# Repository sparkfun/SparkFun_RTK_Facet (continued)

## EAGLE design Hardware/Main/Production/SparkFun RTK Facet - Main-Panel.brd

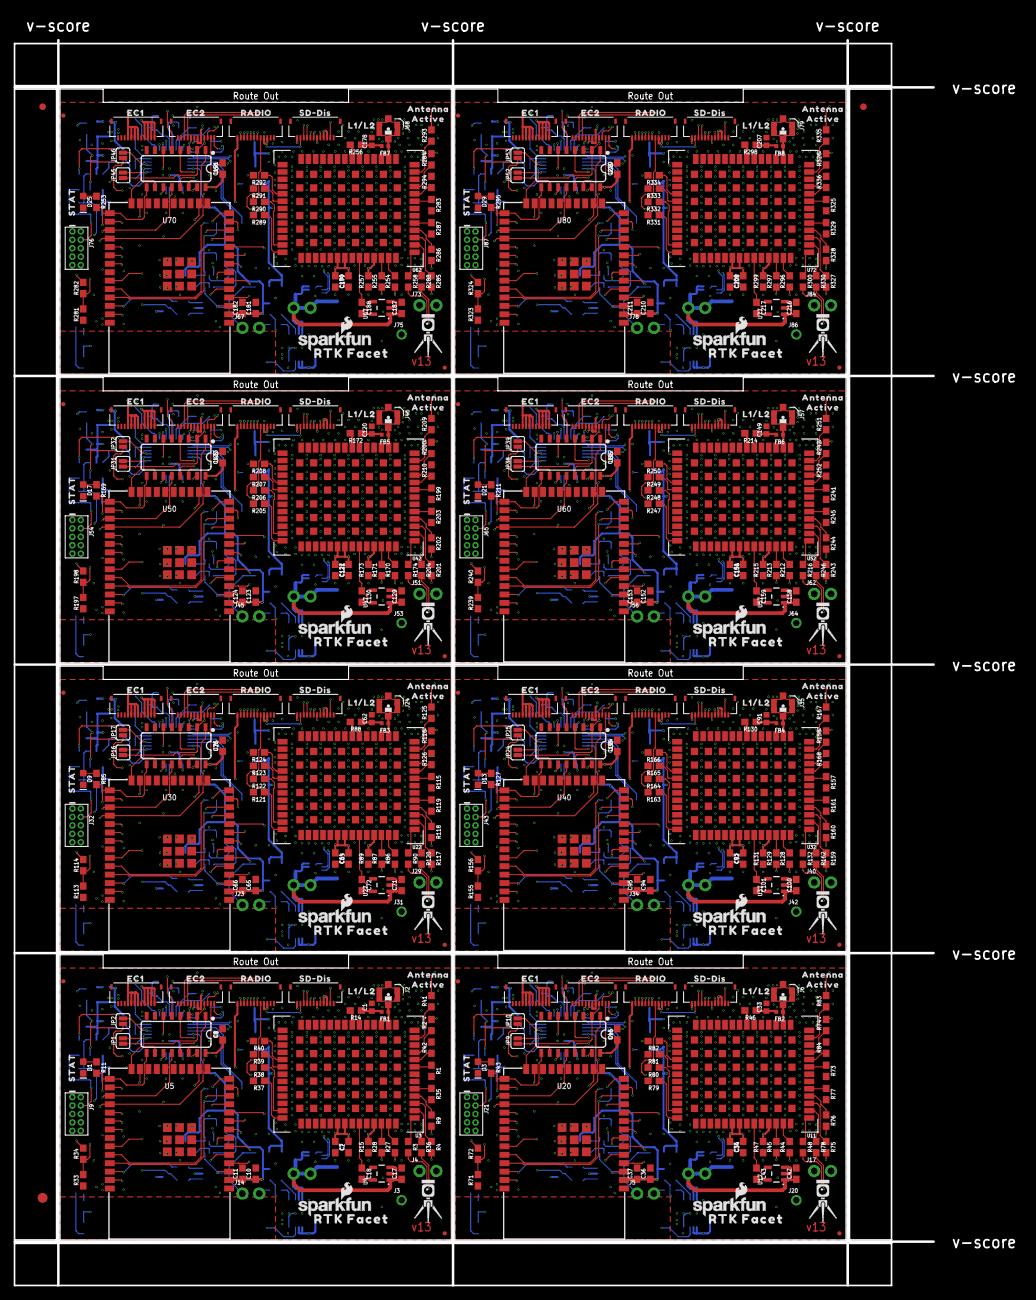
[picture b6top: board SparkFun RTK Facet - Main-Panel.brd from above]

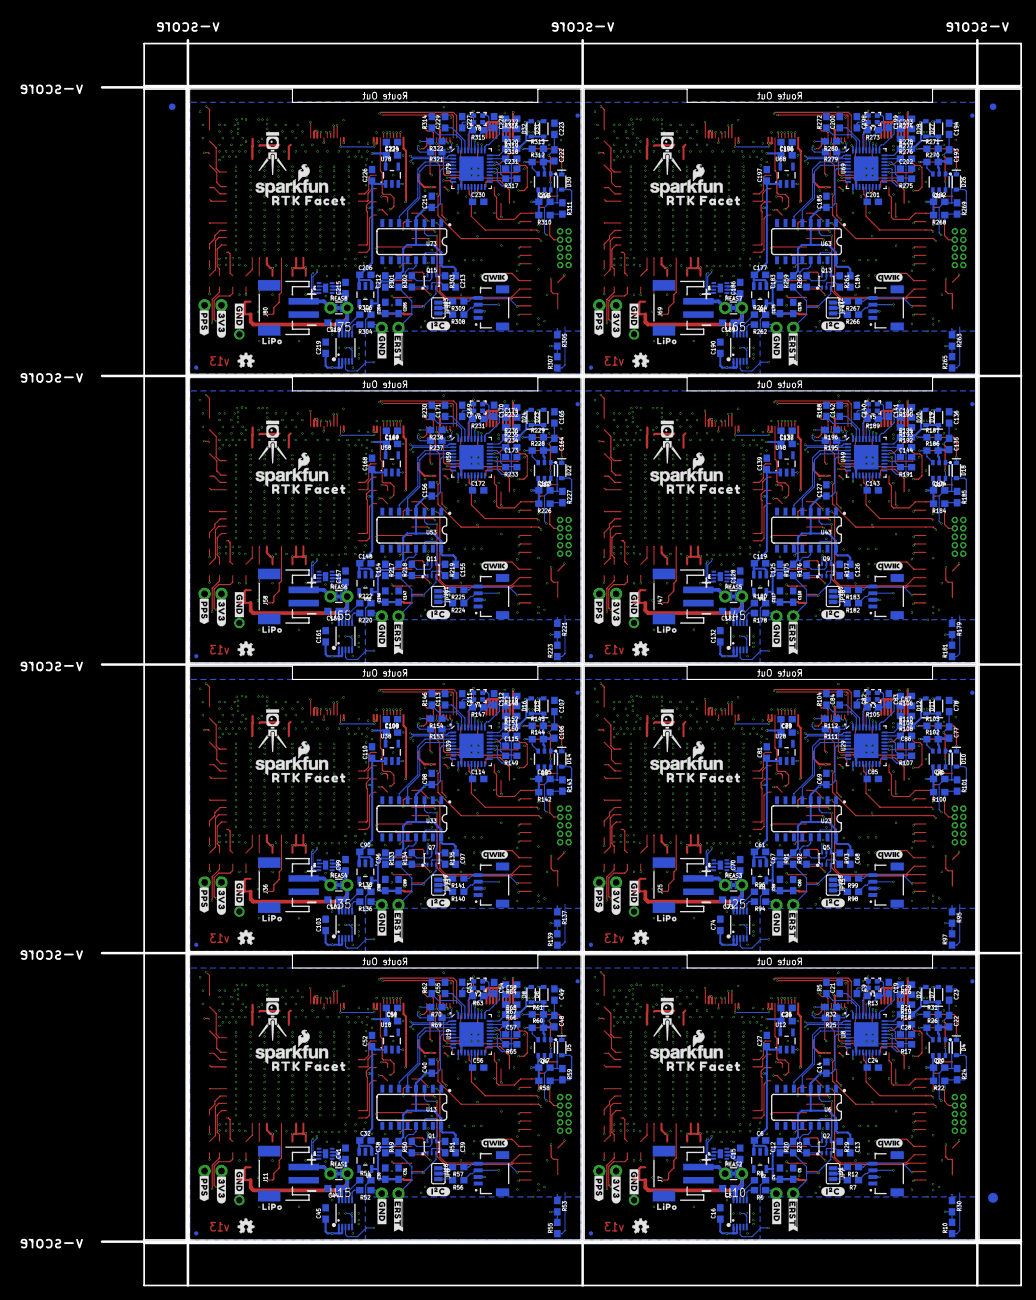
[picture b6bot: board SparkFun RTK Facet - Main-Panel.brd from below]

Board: 4 copper layers, 138.6 x 187.7 mm, 1054 parts (587 on the bottom side), 736 nets.

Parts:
C1, C33, C62, C91, C120, C149, C178, C207: 47pF; 0402
C2, C4, C6, C17, C18, C25, C27, C30, C32, C34, C42, C43, C50, C52, C59, C61, C63, C71, C72, C79, C81, C88, C90, C92, C100, C101, C108, C110, C117, C119, C121, C129, C130, C137, C139, C146, C148, C150, C158, C159, C166, C168, C175, C177, C179, C187, C188, C195, C197, C204, C206, C208, C216, C217, C224, C226: 1.0uF; 0603
C3, C16, C44, C45, C73, C74, C102, C103, C131, C132, C160, C161, C189, C190, C218, C219: 4.7uF; 0603
C5, C7, C8, C11, C12, C13, C15, C21, C22, C23, C24, C26, C28, C29, C31, C35, C37, C38, C39, C41, C46, C48, C49, C51, C55, C56, C57, C58, C60, C64, C66, C67, C68, C70, C75, C77, C78, C80, C84, C85, C86, C87, C89, C93, C95, C96, C97, C99, C104, C106, C107, C109, C113, C114, C115, C116, C118, C122, C124, C125, C126, C128, C133, C135, C136, C138, C142, C143, C144, C145, C147, C151, C153, C154, C155, C157, C162, C164, C165, C167, C171, C172, C173, C174, C176, C180, C182, C183, C184, C186, C191, C193, C194, C196, C200, C201, C202, C203, C205, C209, C211, C212, C213, C215, C220, C222, C223, C225, C229, C230, C231, C232: 0.1uF; 0603
C9, C19, C53, C54, C82, C83, C111, C112, C140, C141, C169, C170, C198, C199, C227, C228: 18pF; 0603
C10, C14, C20, C36, C40, C47, C65, C69, C76, C94, C98, C105, C123, C127, C134, C152, C156, C163, C181, C185, C192, C210, C214, C221: 10uF; 0603
D1, D3, D9, D13, D17, D21, D25, D29: Yellow; LED-0603
D2, D6, D7, D8, D11, D12, D15, D16, D19, D20, D23, D24, D27, D28, D31, D32: 3A/10V/280mV; SOD-323
D4, D5, D10, D14, D18, D22, D26, D30: 250mA/100V; SOD-323
E$1, E$2, E$3, E$4: FIDUCIAL-1X2
E$5, E$6: FIDUCIAL-1.5X3
FB1, FB2, FB3, FB4, FB5, FB6, FB7, FB8: 2.66Ω; 0402-TIGHT
J1, J16, J28, J39, J50, J61, J72, J83: QWIIC_RIGHT_ANGLE; JST04_1MM_RA
J2, J6, J24, J35, J46, J57, J68, J79: U.FL
J3, J20, J31, J42, J53, J64, J75, J86: 1X01_NO_SILK
J4, J5, J14, J17, J23, J29, J34, J40, J45, J51, J56, J62, J67, J73, J78, J84: 1X02_NO_SILK
J7, J11, J25, J36, J47, J58, J69, J80: JST-2-SMD
J8, J10, J12, J13, J15, J18, J19, J22, J26, J27, J30, J33, J37, J38, J41, J44, J48, J49, J52, J55, J59, J60, J63, J66, J70, J71, J74, J77, J81, J82, J85, J88: FPC_12_DOUBLESIDED_BACKFLIP
J9, J21, J32, J43, J54, J65, J76, J87: CORTEX_JTAG_DEBUG_PTH; 2X5-PTH-1.27MM
JP1, JP2, JP9, JP10, JP16, JP17, JP24, JP25, JP31, JP32, JP38, JP39, JP45, JP46, JP52, JP53: JUMPER-SMT_2_NO_SILK; SMT-JUMPER_2_NO_SILK
JP3, JP4, JP5, JP6, JP11, JP12, JP13, JP14, JP18, JP19, JP20, JP21, JP22, JP26, JP27, JP28, JP29, JP33, JP34, JP35, JP36, JP40, JP41, JP42, JP43, JP47, JP48, JP49, JP50, JP61, JP71, JP81: FIDUCIALUFIDUCIAL; FIDUCIAL-MICRO
JP7, JP8, JP15, JP23, JP30, JP37, JP44, JP51: JUMPER-SMT_3_NO_SILK; SMT-JUMPER_3_NO_SILK
LOGO1, LOGO4, LOGO7, LOGO10, LOGO13, LOGO16, LOGO19, LOGO22: OSHW-LOGOMINI; OSHW-LOGO-MINI
LOGO2, LOGO3, LOGO5, LOGO6, LOGO8, LOGO9, LOGO11, LOGO12, LOGO14, LOGO15, LOGO17, LOGO18, LOGO20, LOGO21, LOGO23, LOGO24: SFE_LOGO_NAME_FLAME.1_INCH; SFE_LOGO_NAME_FLAME_.1
MEAS1, MEAS2, MEAS3, MEAS4, MEAS5, MEAS6, MEAS7, MEAS8: JUMPER-COMBO_2_NC_TRACE; COMBO-JUMPER_2_NC_TRACE
Q1, Q2, Q5, Q7, Q9, Q11, Q13, Q15: MBT3904DW1T1; SC70-6
Q3, Q4, Q6, Q8, Q10, Q12, Q14, Q16: SIL2308; SOT26
R1, R2, R3, R4, R9, R35, R36, R37, R38, R39, R40, R41, R42, R48, R73, R74, R75, R76, R77, R78, R79, R80, R81, R82, R83, R84, R90, R115, R116, R117, R118, R119, R120, R121, R122, R123, R124, R125, R126, R132, R157, R158, R159, R160, R161, R162, R163, R164, R165, R166, R167, R168, R174, R199, R200, R201, R202, R203, R204, R205, R206, R207, R208, R209, R210, R216, R241, R242, R243, R244, R245, R246, R247, R248, R249, R250, R251, R252, R258, R283, R284, R285, R286, R287, R288, R289, R290, R291, R292, R293, R294, R300, R325, R326, R327, R328, R329, R330, R331, R332, R333, R334, R335, R336: 33; 0603
R5, R62, R104, R146, R188, R230, R272, R314: 12k; 0603
R6, R11, R43, R52, R85, R94, R127, R136, R169, R178, R211, R220, R253, R262, R295, R304: 1k; 0603
R7, R12, R56, R57, R98, R99, R140, R141, R182, R183, R224, R225, R266, R267, R308, R309: 2.2k; 0603
R8, R54, R96, R138, R180, R222, R264, R306: 0; 0603
R10, R20, R22, R23, R29, R31, R33, R34, R49, R50, R51, R55, R58, R61, R71, R72, R91, R92, R93, R97, R100, R103, R113, R114, R133, R134, R135, R139, R142, R145, R155, R156, R175, R176, R177, R181, R184, R187, R197, R198, R217, R218, R219, R223, R226, R229, R239, R240, R259, R260, R261, R265, R268, R271, R281, R282, R301, R302, R303, R307, R310, R313, R323, R324: 10k; 0603
R13, R63, R105, R147, R189, R231, R273, R315: 1M; 0603
R14, R46, R88, R130, R172, R214, R256, R298: 10; 0603
R15, R16, R17, R18, R19, R21, R26, R47, R60, R64, R65, R66, R67, R68, R89, R102, R106, R107, R108, R109, R110, R131, R144, R148, R149, R150, R151, R152, R173, R186, R190, R191, R192, R193, R194, R215, R228, R232, R233, R234, R235, R236, R257, R270, R274, R275, R276, R277, R278, R299, R312, R316, R317, R318, R319, R320: 100k; 0603
R24, R59, R101, R143, R185, R227, R269, R311: 300k; 0603
R25, R32, R69, R70, R111, R112, R153, R154, R195, R196, R237, R238, R279, R280, R321, R322: 22Ω; 0603
R27, R28, R44, R45, R86, R87, R128, R129, R170, R171, R212, R213, R254, R255, R296, R297: 27; 0603
R30, R53, R95, R137, R179, R221, R263, R305: 150k; 0603
U1, U16, U26, U36, U46, U56, U66, U76: 74HC4052D; SO16
U2, U9, U12, U18, U21, U28, U31, U38, U41, U48, U51, U58, U61, U68, U71, U78: AP2112K-3.3V; SOT23-5
U3, U11, U22, U32, U42, U52, U62, U72: U-BLOX_ZED-F9P; ZED-F9P
U4, U17, U27, U37, U47, U57, U67, U77: STLQ015; SOT23-5
U5, U20, U30, U40, U50, U60, U70, U80: ESP-WROOM-3232D-DFMP; ESP-WROOM-32D-DFM_PASTE
U6, U13, U23, U33, U43, U53, U63, U73: CH340C; SO016
U7, U14, U24, U34, U44, U54, U64, U74: MAX17048; DFN-8
U8, U19, U29, U39, U49, U59, U69, U79: USB251XB; QFN-36
U10, U15, U25, U35, U45, U55, U65, U75: MCP73833MSOP; MSOP10
U$1, U$21, U$45, U$65, U$86, U$106, U$126, U$146: LIPO0
U$2, U$30, U$40, U$60, U$80, U$101, U$121, U$141: QWIIC_4MM
U$3, U$19, U$43, U$63, U$83, U$104, U$124, U$144: EC21
U$4, U$20, U$44, U$64, U$85, U$105, U$125, U$145: SD#DIS0
U$5, U$22, U$46, U$66, U$87, U$107, U$127, U$147: ACTIVE1
U$6, U$28, U$49, U$69, U$90, U$110, U$130, U$150: #3V3#0
U$7, U$23, U$47, U$67, U$88, U$108, U$128, U$148: ANTENNA2
U$8, U$18, U$42, U$62, U$82, U$103, U$123, U$143: EC10
U$9, U$27, U$48, U$68, U$89, U$109, U$129, U$149: L1#L20
U$10, U$29, U$50, U$70, U$91, U$111, U$131, U$151: #PPS#1
U$11, U$13, U$34, U$36, U$54, U$56, U$74, U$76, U$95, U$97, U$115, U$117, U$135, U$137, U$155, U$157: RTK_FACET0
U$12, U$35, U$55, U$75, U$96, U$116, U$136, U$156: RADIO0
U$14, U$17, U$37, U$41, U$57, U$61, U$77, U$81, U$84, U$98, U$102, U$118, U$122, U$138, U$142, U$158: #GND#1
U$15, U$16, U$38, U$39, U$58, U$59, U$78, U$79, U$99, U$100, U$119, U$120, U$139, U$140, U$159, U$160: RTK5#SVG0
U$24, U$31, U$51, U$71, U$92, U$112, U$132, U$152: STAT0
U$25, U$32, U$52, U$72, U$93, U$113, U$133, U$153: #I�C#0
U$26, U$33, U$53, U$73, U$94, U$114, U$134, U$154: ##ERST##0
Y1, Y2, Y3, Y4, Y5, Y6, Y7, Y8: 24MHz; CRYSTAL-SMD-2.0X1.6MM

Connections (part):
3.3V: C2.1, C7.2, C8.1, C25.1, C26.2, J1.2, J4.1, J8.3, J8.4, J10.3, J10.4, J18.5, J18.6, JP7.2, R15.2, U1.16, U3.33, U3.34, U3.38, U12.5
3.3V1: C34.1, C35.2, C46.1, C50.1, C51.2, J13.5, J13.6, J16.2, J17.1, J19.3, J19.4, J22.3, J22.4, JP8.2, R47.2, U11.33, U11.34, U11.38, U16.16, U18.5
3.3V2: C63.1, C64.2, C75.1, C79.1, C80.2, J27.5, J27.6, J28.2, J29.1, J30.3, J30.4, J33.3, J33.4, JP15.2, R89.2, U22.33, U22.34, U22.38, U26.16, U28.5
3.3V3: C92.1, C93.2, C104.1, C108.1, C109.2, J38.5, J38.6, J39.2, J40.1, J41.3, J41.4, J44.3, J44.4, JP23.2, R131.2, U32.33, U32.34, U32.38, U36.16, U38.5
3.3V4: C121.1, C122.2, C133.1, C137.1, C138.2, J49.5, J49.6, J50.2, J51.1, J52.3, J52.4, J55.3, J55.4, JP30.2, R173.2, U42.33, U42.34, U42.38, U46.16, U48.5
3.3V5: C150.1, C151.2, C162.1, C166.1, C167.2, J60.5, J60.6, J61.2, J62.1, J63.3, J63.4, J66.3, J66.4, JP37.2, R215.2, U52.33, U52.34, U52.38, U56.16, U58.5
3.3V6: C179.1, C180.2, C191.1, C195.1, C196.2, J71.5, J71.6, J72.2, J73.1, J74.3, J74.4, J77.3, J77.4, JP44.2, R257.2, U62.33, U62.34, U62.38, U66.16, U68.5
3.3V7: C208.1, C209.2, C220.1, C224.1, C225.2, J82.5, J82.6, J83.2, J84.1, J85.3, J85.4, J88.3, J88.4, JP51.2, R299.2, U72.33, U72.34, U72.38, U76.16, U78.5
ANT_VCC: C1.1, FB1.2, R14.1
ANT_VCC1: C33.1, FB2.2, R46.1
ANT_VCC2: C62.1, FB3.2, R88.1
ANT_VCC3: C91.1, FB4.2, R130.1
ANT_VCC4: C120.1, FB5.2, R172.1
ANT_VCC5: C149.1, FB6.2, R214.1
ANT_VCC6: C178.1, FB7.2, R256.1
ANT_VCC7: C207.1, FB8.2, R298.1
CHG_LED: J8.11, U10.3
CHG_LED1: J19.11, U15.3
CHG_LED2: J30.11, U25.3
CHG_LED3: J41.11, U35.3
CHG_LED4: J52.11, U45.3
CHG_LED5: J63.11, U55.3
CHG_LED6: J74.11, U65.3
CHG_LED7: J85.11, U75.3
CHG_THERM1: R8.2, R10.2, R30.2
CHG_THERM2: R53.2, R54.2, R55.2
CHG_THERM3: R95.2, R96.2, R97.2
CHG_THERM4: R137.2, R138.2, R139.2
CHG_THERM5: R179.2, R180.2, R181.2
CHG_THERM6: R221.2, R222.2, R223.2
CHG_THERM7: R263.2, R264.2, R265.2
CHG_THERM8: R305.2, R306.2, R307.2
ESP32_!DTR: Q2.1, R23.1, U6.13
ESP32_!DTR1: Q1.1, R50.1, U13.13
ESP32_!DTR2: Q5.1, R92.1, U23.13
ESP32_!DTR3: Q7.1, R134.1, U33.13
ESP32_!DTR4: Q9.1, R176.1, U43.13
ESP32_!DTR5: Q11.1, R218.1, U53.13
ESP32_!DTR6: Q13.1, R260.1, U63.13
ESP32_!DTR7: Q15.1, R302.1, U73.13
ESP32_!RTS: Q2.4, R29.1, U6.14
ESP32_!RTS1: Q1.4, R51.1, U13.14
ESP32_!RTS2: Q5.4, R93.1, U23.14
ESP32_!RTS3: Q7.4, R135.1, U33.14
ESP32_!RTS4: Q9.4, R177.1, U43.14
ESP32_!RTS5: Q11.4, R219.1, U53.14
ESP32_!RTS6: Q13.4, R261.1, U63.14
ESP32_!RTS7: Q15.4, R303.1, U73.14
ESP32_EN: C12.1, J9.10, J14.1, Q2.3, R20.1, U5.3
ESP32_EN1: C38.1, J5.1, J21.10, Q1.3, R49.1, U20.3
ESP32_EN2: C67.1, J23.1, J32.10, Q5.3, R91.1, U30.3
ESP32_EN3: C96.1, J34.1, J43.10, Q7.3, R133.1, U40.3
ESP32_EN4: C125.1, J45.1, J54.10, Q9.3, R175.1, U50.3
ESP32_EN5: C154.1, J56.1, J65.10, Q11.3, R217.1, U60.3
ESP32_EN6: C183.1, J67.1, J76.10, Q13.3, R259.1, U70.3
ESP32_EN7: C212.1, J78.1, J87.10, Q15.3, R301.1, U80.3
ESP32_RXI: U5.34, U6.2
ESP32_RXI1: U13.2, U20.34
ESP32_RXI2: U23.2, U30.34
ESP32_RXI3: U33.2, U40.34
ESP32_RXI4: U43.2, U50.34
ESP32_RXI5: U53.2, U60.34
ESP32_RXI6: U63.2, U70.34
ESP32_RXI7: U73.2, U80.34
ESP32_TXO: U5.35, U6.3
ESP32_TXO1: U13.3, U20.35
ESP32_TXO2: U23.3, U30.35
ESP32_TXO3: U33.3, U40.35
ESP32_TXO4: U43.3, U50.35
ESP32_TXO5: U53.3, U60.35
ESP32_TXO6: U63.3, U70.35
ESP32_TXO7: U73.3, U80.35
ESP_0/BOOT/STAT_LED/MUX_B: Q2.6, R11.2, U1.9, U5.25
ESP_0/BOOT/STAT_LED/MUX_B1: Q1.6, R43.2, U16.9, U20.25
ESP_0/BOOT/STAT_LED/MUX_B2: Q5.6, R85.2, U26.9, U30.25
ESP_0/BOOT/STAT_LED/MUX_B3: Q7.6, R127.2, U36.9, U40.25
ESP_0/BOOT/STAT_LED/MUX_B4: Q9.6, R169.2, U46.9, U50.25
ESP_0/BOOT/STAT_LED/MUX_B5: Q11.6, R211.2, U56.9, U60.25
ESP_0/BOOT/STAT_LED/MUX_B6: Q13.6, R253.2, U66.9, U70.25
ESP_0/BOOT/STAT_LED/MUX_B7: Q15.6, R295.2, U76.9, U80.25
ESP_2/MUX_A: U1.10, U5.24
ESP_2/MUX_A1: U16.10, U20.24
ESP_2/MUX_A2: U26.10, U30.24
ESP_2/MUX_A3: U36.10, U40.24
ESP_2/MUX_A4: U46.10, U50.24
ESP_2/MUX_A5: U56.10, U60.24
ESP_2/MUX_A6: U66.10, U70.24
ESP_2/MUX_A7: U76.10, U80.24
ESP_3V1: C30.1, C31.2, C36.1, C37.1, C39.1, C40.1, J21.1, R49.2, R66.2, R72.2, U9.5, U13.4, U13.16, U19.5, U19.10, U19.15, U19.23, U19.29, U19.36, U20.2
ESP_3V2: C59.1, C60.2, C65.1, C66.1, C68.1, C69.1, J32.1, R91.2, R108.2, R114.2, U21.5, U23.4, U23.16, U29.5, U29.10, U29.15, U29.23, U29.29, U29.36, U30.2
ESP_3V3: C4.1, C5.2, C10.1, C11.1, C13.1, C14.1, J9.1, R18.2, R20.2, R34.2, U2.5, U5.2, U6.4, U6.16, U8.5, U8.10, U8.15, U8.23, U8.29, U8.36
ESP_3V4: C88.1, C89.2, C94.1, C95.1, C97.1, C98.1, J43.1, R133.2, R150.2, R156.2, U31.5, U33.4, U33.16, U39.5, U39.10, U39.15, U39.23, U39.29, U39.36, U40.2
ESP_3V5: C117.1, C118.2, C123.1, C124.1, C126.1, C127.1, J54.1, R175.2, R192.2, R198.2, U41.5, U43.4, U43.16, U49.5, U49.10, U49.15, U49.23, U49.29, U49.36, U50.2
ESP_3V6: C146.1, C147.2, C152.1, C153.1, C155.1, C156.1, J65.1, R217.2, R234.2, R240.2, U51.5, U53.4, U53.16, U59.5, U59.10, U59.15, U59.23, U59.29, U59.36, U60.2
ESP_3V7: C175.1, C176.2, C181.1, C182.1, C184.1, C185.1, J76.1, R259.2, R276.2, R282.2, U61.5, U63.4, U63.16, U69.5, U69.10, U69.15, U69.23, U69.29, U69.36, U70.2
ESP_3V8: C204.1, C205.2, C210.1, C211.1, C213.1, C214.1, J87.1, R301.2, R318.2, R324.2, U71.5, U73.4, U73.16, U79.5, U79.10, U79.15, U79.23, U79.29, U79.36, U80.2
ESP_4/RADIO_PWR_ON: J10.6, U5.26
ESP_4/RADIO_PWR_ON1: J22.6, U20.26
ESP_4/RADIO_PWR_ON2: J33.6, U30.26
ESP_4/RADIO_PWR_ON3: J44.6, U40.26
ESP_4/RADIO_PWR_ON4: J55.6, U50.26
ESP_4/RADIO_PWR_ON5: J66.6, U60.26
ESP_4/RADIO_PWR_ON6: J77.6, U70.26
ESP_4/RADIO_PWR_ON7: J88.6, U80.26
ESP_5/RADIO_CTSI: J10.8, U5.29
ESP_5/RADIO_CTSI1: J22.8, U20.29
ESP_5/RADIO_CTSI2: J33.8, U30.29
ESP_5/RADIO_CTSI3: J44.8, U40.29
ESP_5/RADIO_CTSI4: J55.8, U50.29
ESP_5/RADIO_CTSI5: J66.8, U60.29
ESP_5/RADIO_CTSI6: J77.8, U70.29
ESP_5/RADIO_CTSI7: J88.8, U80.29
ESP_12/MTDI: J9.8, U5.14
ESP_12/MTDI1: J21.8, U20.14
ESP_12/MTDI2: J32.8, U30.14
ESP_12/MTDI3: J43.8, U40.14
ESP_12/MTDI4: J54.8, U50.14
ESP_12/MTDI5: J65.8, U60.14
ESP_12/MTDI6: J76.8, U70.14
ESP_12/MTDI7: J87.8, U80.14
ESP_13/POWER_CTRL/MTCK: D4.A, J9.4, R22.1, R24.2, U5.16
ESP_13/POWER_CTRL/MTCK1: D5.A, J21.4, R58.1, R59.2, U20.16
ESP_13/POWER_CTRL/MTCK2: D10.A, J32.4, R100.1, R101.2, U30.16
ESP_13/POWER_CTRL/MTCK3: D14.A, J43.4, R142.1, R143.2, U40.16
ESP_13/POWER_CTRL/MTCK4: D18.A, J54.4, R184.1, R185.2, U50.16
ESP_13/POWER_CTRL/MTCK5: D22.A, J65.4, R226.1, R227.2, U60.16
ESP_13/POWER_CTRL/MTCK6: D26.A, J76.4, R268.1, R269.2, U70.16
ESP_13/POWER_CTRL/MTCK7: D30.A, J87.4, R310.1, R311.2, U80.16
ESP_14/PERIPHERAL_POWER/MTMS: J9.2, U5.13, U12.3
ESP_14/PERIPHERAL_POWER/MTMS1: J21.2, U18.3, U20.13
ESP_14/PERIPHERAL_POWER/MTMS2: J32.2, U28.3, U30.13
ESP_14/PERIPHERAL_POWER/MTMS3: J43.2, U38.3, U40.13
ESP_14/PERIPHERAL_POWER/MTMS4: J54.2, U48.3, U50.13
ESP_14/PERIPHERAL_POWER/MTMS5: J65.2, U58.3, U60.13
ESP_14/PERIPHERAL_POWER/MTMS6: J76.2, U68.3, U70.13
ESP_14/PERIPHERAL_POWER/MTMS7: J87.2, U78.3, U80.13
ESP_15/MTDO/RADIO_!RESET!: J9.6, J10.5, U5.23
ESP_15/MTDO/RADIO_!RESET!1: J21.6, J22.5, U20.23
ESP_15/MTDO/RADIO_!RESET!2: J32.6, J33.5, U30.23
ESP_15/MTDO/RADIO_!RESET!3: J43.6, J44.5, U40.23
ESP_15/MTDO/RADIO_!RESET!4: J54.6, J55.5, U50.23
ESP_15/MTDO/RADIO_!RESET!5: J65.6, J66.5, U60.23
ESP_15/MTDO/RADIO_!RESET!6: J76.6, J77.5, U70.23
ESP_15/MTDO/RADIO_!RESET!7: J87.6, J88.5, U80.23
ESP_16/ZED-TXO1: R3.2, U1.12, U5.27
ESP_16/ZED-TXO2: R48.2, U16.12, U20.27
ESP_16/ZED-TXO3: R90.2, U26.12, U30.27
ESP_16/ZED-TXO4: R132.2, U36.12, U40.27
ESP_16/ZED-TXO5: R174.2, U46.12, U50.27
ESP_16/ZED-TXO6: R216.2, U56.12, U60.27
ESP_16/ZED-TXO7: R258.2, U66.12, U70.27
ESP_16/ZED-TXO8: R300.2, U76.12, U80.27
ESP_17/ZED-RXI1: R36.2, U1.1, U5.28
ESP_17/ZED-RXI2: R78.2, U16.1, U20.28
ESP_17/ZED-RXI3: R120.2, U26.1, U30.28
ESP_17/ZED-RXI4: R162.2, U36.1, U40.28
ESP_17/ZED-RXI5: R204.2, U46.1, U50.28
ESP_17/ZED-RXI6: R246.2, U56.1, U60.28
ESP_17/ZED-RXI7: R288.2, U66.1, U70.28
ESP_17/ZED-RXI8: R330.2, U76.1, U80.28
ESP_18/SD_SCK: J8.7, U5.30
ESP_18/SD_SCK1: J19.7, U20.30
ESP_18/SD_SCK2: J30.7, U30.30
ESP_18/SD_SCK3: J41.7, U40.30
ESP_18/SD_SCK4: J52.7, U50.30
ESP_18/SD_SCK5: J63.7, U60.30
ESP_18/SD_SCK6: J74.7, U70.30
ESP_18/SD_SCK7: J85.7, U80.30
ESP_19/SD_CIPO: J8.8, U5.31
ESP_19/SD_CIPO1: J19.8, U20.31
ESP_19/SD_CIPO2: J30.8, U30.31
ESP_19/SD_CIPO3: J41.8, U40.31
ESP_19/SD_CIPO4: J52.8, U50.31
ESP_19/SD_CIPO5: J63.8, U60.31
ESP_19/SD_CIPO6: J74.8, U70.31
ESP_19/SD_CIPO7: J85.8, U80.31
ESP_21/SDA: J1.3, J8.10, J18.4, JP1.1, R4.2, R7.1, U1.2, U5.33, U7.8
ESP_21/SDA1: J13.4, J16.3, J19.10, JP9.1, R56.1, R75.2, U14.8, U16.2, U20.33
ESP_21/SDA2: J27.4, J28.3, J30.10, JP16.1, R98.1, R117.2, U24.8, U26.2, U30.33
ESP_21/SDA3: J38.4, J39.3, J41.10, JP24.1, R140.1, R159.2, U34.8, U36.2, U40.33
ESP_21/SDA4: J49.4, J50.3, J52.10, JP31.1, R182.1, R201.2, U44.8, U46.2, U50.33
ESP_21/SDA5: J60.4, J61.3, J63.10, JP38.1, R224.1, R243.2, U54.8, U56.2, U60.33
ESP_21/SDA6: J71.4, J72.3, J74.10, JP45.1, R266.1, R285.2, U64.8, U66.2, U70.33
ESP_21/SDA7: J82.4, J83.3, J85.10, JP52.1, R308.1, R327.2, U74.8, U76.2, U80.33
ESP_22/SCL: J1.4, J8.9, J18.3, JP2.1, R9.2, R12.1, U1.15, U5.36, U7.7
ESP_22/SCL1: J13.3, J16.4, J19.9, JP10.1, R57.1, R76.2, U14.7, U16.15, U20.36
ESP_22/SCL2: J27.3, J28.4, J30.9, JP17.1, R99.1, R118.2, U24.7, U26.15, U30.36
ESP_22/SCL3: J38.3, J39.4, J41.9, JP25.1, R141.1, R160.2, U34.7, U36.15, U40.36
ESP_22/SCL4: J49.3, J50.4, J52.9, JP32.1, R183.1, R202.2, U44.7, U46.15, U50.36
ESP_22/SCL5: J60.3, J61.4, J63.9, JP39.1, R225.1, R244.2, U54.7, U56.15, U60.36
ESP_22/SCL6: J71.3, J72.4, J74.9, JP46.1, R267.1, R286.2, U64.7, U66.15, U70.36
ESP_22/SCL7: J82.3, J83.4, J85.9, JP53.1, R309.1, R328.2, U74.7, U76.15, U80.36
ESP_23/SD_COPI: J8.6, U5.37
ESP_23/SD_COPI1: J19.6, U20.37
ESP_23/SD_COPI2: J30.6, U30.37
ESP_23/SD_COPI3: J41.6, U40.37
ESP_23/SD_COPI4: J52.6, U50.37
ESP_23/SD_COPI5: J63.6, U60.37
ESP_23/SD_COPI6: J74.6, U70.37
ESP_23/SD_COPI7: J85.6, U80.37
ESP_25/SD_!CS!: J8.5, U5.10
ESP_25/SD_!CS!1: J19.5, U20.10
ESP_25/SD_!CS!2: J30.5, U30.10
ESP_25/SD_!CS!3: J41.5, U40.10
ESP_25/SD_!CS!4: J52.5, U50.10
ESP_25/SD_!CS!5: J63.5, U60.10
ESP_25/SD_!CS!6: J74.5, U70.10
ESP_25/SD_!CS!7: J85.5, U80.10
ESP_26/DAC1: U16.11, U20.11
ESP_26/DAC2: U1.11, U5.11
ESP_26/DAC3: U26.11, U30.11
ESP_26/DAC4: U36.11, U40.11
ESP_26/DAC5: U46.11, U50.11
ESP_26/DAC6: U56.11, U60.11
ESP_26/DAC7: U66.11, U70.11
ESP_26/DAC8: U76.11, U80.11
ESP_27/FAST_OFF: C20.2, Q3.G1, R24.1, U5.12
ESP_27/FAST_OFF1: C47.2, Q4.G1, R59.1, U20.12
ESP_27/FAST_OFF2: C76.2, Q6.G1, R101.1, U30.12
ESP_27/FAST_OFF3: C105.2, Q8.G1, R143.1, U40.12
ESP_27/FAST_OFF4: C134.2, Q10.G1, R185.1, U50.12
ESP_27/FAST_OFF5: C163.2, Q12.G1, R227.1, U60.12
ESP_27/FAST_OFF6: C192.2, Q14.G1, R269.1, U70.12
ESP_27/FAST_OFF7: C221.2, Q16.G1, R311.1, U80.12
ESP_32/RADIO_TXO: J10.11, U5.8
ESP_32/RADIO_TXO1: J22.11, U20.8
ESP_32/RADIO_TXO2: J33.11, U30.8
ESP_32/RADIO_TXO3: J44.11, U40.8
ESP_32/RADIO_TXO4: J55.11, U50.8
ESP_32/RADIO_TXO5: J66.11, U60.8
ESP_32/RADIO_TXO6: J77.11, U70.8
ESP_32/RADIO_TXO7: J88.11, U80.8
ESP_33/RADIO_RXI: J10.10, U5.9
ESP_33/RADIO_RXI1: J22.10, U20.9
ESP_33/RADIO_RXI2: J33.10, U30.9
ESP_33/RADIO_RXI3: J44.10, U40.9
ESP_33/RADIO_RXI4: J55.10, U50.9
ESP_33/RADIO_RXI5: J66.10, U60.9
ESP_33/RADIO_RXI6: J77.10, U70.9
ESP_33/RADIO_RXI7: J88.10, U80.9
ESP_DM: U6.6, U8.3
ESP_DM1: U13.6, U19.3
ESP_DM2: U23.6, U29.3
ESP_DM3: U33.6, U39.3
ESP_DM4: U43.6, U49.3
ESP_DM5: U53.6, U59.3
ESP_DM6: U63.6, U69.3
ESP_DM7: U73.6, U79.3
ESP_DP: U6.5, U8.4
ESP_DP1: U13.5, U19.4
ESP_DP2: U23.5, U29.4
ESP_DP3: U33.5, U39.4
ESP_DP4: U43.5, U49.4
ESP_DP5: U53.5, U59.4
ESP_DP6: U63.5, U69.4
ESP_DP7: U73.5, U79.4
ESP_I34/RADIO_INT: J10.7, U5.6
ESP_I34/RADIO_INT1: J22.7, U20.6
ESP_I34/RADIO_INT2: J33.7, U30.6
ESP_I34/RADIO_INT3: J44.7, U40.6
ESP_I34/RADIO_INT4: J55.7, U50.6
ESP_I34/RADIO_INT5: J66.7, U60.6
ESP_I34/RADIO_INT6: J77.7, U70.6
ESP_I34/RADIO_INT7: J88.7, U80.6
ESP_I35/DEVICE_SENSE: R33.2, R34.1, U5.7
ESP_I35/DEVICE_SENSE1: R71.2, R72.1, U20.7
ESP_I35/DEVICE_SENSE2: R113.2, R114.1, U30.7
ESP_I35/DEVICE_SENSE3: R155.2, R156.1, U40.7
ESP_I35/DEVICE_SENSE4: R197.2, R198.1, U50.7
ESP_I35/DEVICE_SENSE5: R239.2, R240.1, U60.7
ESP_I35/DEVICE_SENSE6: R281.2, R282.1, U70.7
ESP_I35/DEVICE_SENSE7: R323.2, R324.1, U80.7
ESP_I36/RADIO_RTSO: J10.9, U5.4
ESP_I36/RADIO_RTSO1: J22.9, U20.4
ESP_I36/RADIO_RTSO2: J33.9, U30.4
ESP_I36/RADIO_RTSO3: J44.9, U40.4
ESP_I36/RADIO_RTSO4: J55.9, U50.4
ESP_I36/RADIO_RTSO5: J66.9, U60.4
ESP_I36/RADIO_RTSO6: J77.9, U70.4
ESP_I36/RADIO_RTSO7: J88.9, U80.4
ESP_I39/ADC1: U16.4, U20.5
ESP_I39/ADC2: U26.4, U30.5
ESP_I39/ADC3: U36.4, U40.5
ESP_I39/ADC4: U46.4, U50.5
ESP_I39/ADC5: U56.4, U60.5
ESP_I39/ADC6: U66.4, U70.5
ESP_I39/ADC7: U76.4, U80.5
ESP_I39/ADC39: U1.4, U5.5
EXTERNAL_SERIAL1_RXI: J18.1, U1.3
EXTERNAL_SERIAL1_RXI1: J13.1, U16.3
EXTERNAL_SERIAL1_RXI2: J27.1, U26.3
EXTERNAL_SERIAL1_RXI3: J38.1, U36.3
EXTERNAL_SERIAL1_RXI4: J49.1, U46.3
EXTERNAL_SERIAL1_RXI5: J60.1, U56.3
EXTERNAL_SERIAL1_RXI6: J71.1, U66.3
EXTERNAL_SERIAL1_RXI7: J82.1, U76.3
EXTERNAL_SERIAL1_TXO: J18.2, U1.13
EXTERNAL_SERIAL1_TXO1: J13.2, U16.13
EXTERNAL_SERIAL1_TXO2: J27.2, U26.13
EXTERNAL_SERIAL1_TXO3: J38.2, U36.13
EXTERNAL_SERIAL1_TXO4: J49.2, U46.13
EXTERNAL_SERIAL1_TXO5: J60.2, U56.13
EXTERNAL_SERIAL1_TXO6: J71.2, U66.13
EXTERNAL_SERIAL1_TXO7: J82.2, U76.13
FENCE_LV: R40.1, U3.19
FENCE_LV1: R82.1, U11.19
FENCE_LV2: R124.1, U22.19
FENCE_LV3: R166.1, U32.19
FENCE_LV4: R208.1, U42.19
FENCE_LV5: R250.1, U52.19
FENCE_LV6: R292.1, U62.19
FENCE_LV7: R334.1, U72.19
GND: C1.2, C2.2, C3.2, C4.2, C5.1, C6.2, C7.1, C8.2, C9.1, C10.2, C11.2, C12.2, C13.2, C14.2, C15.2, C16.2, C17.2, C18.2, C19.1, C21.2, C24.2, C25.2, C26.1, C27.2, C28.2, C29.2, D1.C, J1.1, J2.1, J2.2, J3.1, J7.1, J8.1, J9.3, J9.5, J9.7, J9.9, J10.1, J10.2, J14.2, J15.10, J15.11, J15.12, J18.11, J18.12, Q3.S1, R5.2, R6.1, R10.1, R15.1, R16.1, R17.1, R19.1, R30.1, R33.1, U1.6, U1.7, U1.8, U2.2, U3.1, U3.3, U3.12, U3.14, U3.32, U3.37, U3.41, U3.48, U3.55, U3.56, U3.57, U3.58, U3.59, U3.60, U3.61, U3.62, U3.63, U3.64, U3.65, U3.66, U3.67, U3.68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
GND1: C30.2, C31.1, C32.2, C33.2, C34.2, C35.1, C36.2, C37.2, C38.2, C39.2, C40.2, C41.2, C42.2, C43.2, C44.2, C45.2, C46.2, C50.2, C51.1, C52.2, C53.1, C54.1, C55.2, C56.2, C57.2, C58.2, D3.C, J5.2, J6.1, J6.2, J11.1, J12.10, J12.11, J12.12, J13.11, J13.12, J16.1, J19.1, J20.1, J21.3, J21.5, J21.7, J21.9, J22.1, J22.2, Q4.S1, R47.1, R52.1, R53.1, R55.1, R62.2, R64.1, R65.1, R67.1, R71.1, U9.2, U11.1, U11.3, U11.12, U11.14, U11.32, U11.37, U11.41, U11.48, U11.55, U11.56, U11.57, U11.58, U11.59, U11.60, U11.61, U11.62, U11.63, U11.64, U11.65, U11.66, U11.67, U11.68, U11.69, U11.70, U11.71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
GND2: C59.2, C60.1, C61.2, C62.2, C63.2, C64.1, C65.2, C66.2, C67.2, C68.2, C69.2, C70.2, C71.2, C72.2, C73.2, C74.2, C75.2, C79.2, C80.1, C81.2, C82.1, C83.1, C84.2, C85.2, C86.2, C87.2, D9.C, J23.2, J24.1, J24.2, J25.1, J26.10, J26.11, J26.12, J27.11, J27.12, J28.1, J30.1, J31.1, J32.3, J32.5, J32.7, J32.9, J33.1, J33.2, Q6.S1, R89.1, R94.1, R95.1, R97.1, R104.2, R106.1, R107.1, R109.1, R113.1, U21.2, U22.1, U22.3, U22.12, U22.14, U22.32, U22.37, U22.41, U22.48, U22.55, U22.56, U22.57, U22.58, U22.59, U22.60, U22.61, U22.62, U22.63, U22.64, U22.65, U22.66, U22.67, U22.68, U22.69, U22.70, U22.71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
GND3: C88.2, C89.1, C90.2, C91.2, C92.2, C93.1, C94.2, C95.2, C96.2, C97.2, C98.2, C99.2, C100.2, C101.2, C102.2, C103.2, C104.2, C108.2, C109.1, C110.2, C111.1, C112.1, C113.2, C114.2, C115.2, C116.2, D13.C, J34.2, J35.1, J35.2, J36.1, J37.10, J37.11, J37.12, J38.11, J38.12, J39.1, J41.1, J42.1, J43.3, J43.5, J43.7, J43.9, J44.1, J44.2, Q8.S1, R131.1, R136.1, R137.1, R139.1, R146.2, R148.1, R149.1, R151.1, R155.1, U31.2, U32.1, U32.3, U32.12, U32.14, U32.32, U32.37, U32.41, U32.48, U32.55, U32.56, U32.57, U32.58, U32.59, U32.60, U32.61, U32.62, U32.63, U32.64, U32.65, U32.66, U32.67, U32.68, U32.69, U32.70, U32.71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
GND4: C117.2, C118.1, C119.2, C120.2, C121.2, C122.1, C123.2, C124.2, C125.2, C126.2, C127.2, C128.2, C129.2, C130.2, C131.2, C132.2, C133.2, C137.2, C138.1, C139.2, C140.1, C141.1, C142.2, C143.2, C144.2, C145.2, D17.C, J45.2, J46.1, J46.2, J47.1, J48.10, J48.11, J48.12, J49.11, J49.12, J50.1, J52.1, J53.1, J54.3, J54.5, J54.7, J54.9, J55.1, J55.2, Q10.S1, R173.1, R178.1, R179.1, R181.1, R188.2, R190.1, R191.1, R193.1, R197.1, U41.2, U42.1, U42.3, U42.12, U42.14, U42.32, U42.37, U42.41, U42.48, U42.55, U42.56, U42.57, U42.58, U42.59, U42.60, U42.61, U42.62, U42.63, U42.64, U42.65, U42.66, U42.67, U42.68, U42.69, U42.70, U42.71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
GND5: C146.2, C147.1, C148.2, C149.2, C150.2, C151.1, C152.2, C153.2, C154.2, C155.2, C156.2, C157.2, C158.2, C159.2, C160.2, C161.2, C162.2, C166.2, C167.1, C168.2, C169.1, C170.1, C171.2, C172.2, C173.2, C174.2, D21.C, J56.2, J57.1, J57.2, J58.1, J59.10, J59.11, J59.12, J60.11, J60.12, J61.1, J63.1, J64.1, J65.3, J65.5, J65.7, J65.9, J66.1, J66.2, Q12.S1, R215.1, R220.1, R221.1, R223.1, R230.2, R232.1, R233.1, R235.1, R239.1, U51.2, U52.1, U52.3, U52.12, U52.14, U52.32, U52.37, U52.41, U52.48, U52.55, U52.56, U52.57, U52.58, U52.59, U52.60, U52.61, U52.62, U52.63, U52.64, U52.65, U52.66, U52.67, U52.68, U52.69, U52.70, U52.71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
GND6: C175.2, C176.1, C177.2, C178.2, C179.2, C180.1, C181.2, C182.2, C183.2, C184.2, C185.2, C186.2, C187.2, C188.2, C189.2, C190.2, C191.2, C195.2, C196.1, C197.2, C198.1, C199.1, C200.2, C201.2, C202.2, C203.2, D25.C, J67.2, J68.1, J68.2, J69.1, J70.10, J70.11, J70.12, J71.11, J71.12, J72.1, J74.1, J75.1, J76.3, J76.5, J76.7, J76.9, J77.1, J77.2, Q14.S1, R257.1, R262.1, R263.1, R265.1, R272.2, R274.1, R275.1, R277.1, R281.1, U61.2, U62.1, U62.3, U62.12, U62.14, U62.32, U62.37, U62.41, U62.48, U62.55, U62.56, U62.57, U62.58, U62.59, U62.60, U62.61, U62.62, U62.63, U62.64, U62.65, U62.66, U62.67, U62.68, U62.69, U62.70, U62.71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
GND7: C204.2, C205.1, C206.2, C207.2, C208.2, C209.1, C210.2, C211.2, C212.2, C213.2, C214.2, C215.2, C216.2, C217.2, C218.2, C219.2, C220.2, C224.2, C225.1, C226.2, C227.1, C228.1, C229.2, C230.2, C231.2, C232.2, D29.C, J78.2, J79.1, J79.2, J80.1, J81.10, J81.11, J81.12, J82.11, J82.12, J83.1, J85.1, J86.1, J87.3, J87.5, J87.7, J87.9, J88.1, J88.2, Q16.S1, R299.1, R304.1, R305.1, R307.1, R314.2, R316.1, R317.1, R319.1, R323.1, U71.2, U72.1, U72.3, U72.12, U72.14, U72.32, U72.37, U72.41, U72.48, U72.55, U72.56, U72.57, U72.58, U72.59, U72.60, U72.61, U72.62, U72.63, U72.64, U72.65, U72.66, U72.67, U72.68, U72.69, U72.70, U72.71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
GPS_ANT1: FB1.1, J2.FEED, U3.2
GPS_ANT2: FB2.1, J6.FEED, U11.2
GPS_ANT3: FB3.1, J24.FEED, U22.2
GPS_ANT4: FB4.1, J35.FEED, U32.2
GPS_ANT5: FB5.1, J46.FEED, U42.2
GPS_ANT6: FB6.1, J57.FEED, U52.2
GPS_ANT7: FB7.1, J68.FEED, U62.2
GPS_ANT8: FB8.1, J79.FEED, U72.2
LIPO_RAW: J7.2, MEAS2.1, MEAS2.3
LIPO_RAW1: J11.2, MEAS1.1, MEAS1.3
LIPO_RAW2: J25.2, MEAS3.1, MEAS3.3
LIPO_RAW3: J36.2, MEAS4.1, MEAS4.3
LIPO_RAW4: J47.2, MEAS5.1, MEAS5.3
LIPO_RAW5: J58.2, MEAS6.1, MEAS6.3
LIPO_RAW6: J69.2, MEAS7.1, MEAS7.3
LIPO_RAW7: J80.2, MEAS8.1, MEAS8.3
unnamed: R8.1, U10.8
unnamed: D1.A, R11.1
unnamed: JP7.3, R7.2
unnamed: JP7.1, R12.2
unnamed: R2.1, U3.51
unnamed: C22.1, C23.2, Q3.D1, Q3.G2, R26.1
unnamed: C9.2, R13.2, U8.33, Y1.3
unnamed: C19.2, R13.1, U8.32, Y1.1
unnamed: R5.1, U8.35
unnamed: R16.2, U8.28
unnamed: R27.2, U3.40
unnamed: R28.2, U3.39
unnamed: R14.2, U3.7
unnamed: R17.2, U8.25
unnamed: C21.1, U8.34
unnamed: R1.1, U3.49
unnamed: C24.1, U8.14
unnamed: R42.1, U3.50
unnamed: R25.2, U8.30
unnamed: R32.2, U8.31
unnamed: JP1.2, U8.22
unnamed: R35.1, U3.46
unnamed: JP2.2, U8.24
unnamed: Q2.5, R23.2
unnamed: Q2.2, R29.2
unnamed: D3.A, R43.1
unnamed: R44.2, U11.40
unnamed: R45.2, U11.39
unnamed: R46.2, U11.7
unnamed: R73.1, U11.49
unnamed: R84.1, U11.50
unnamed: R77.1, U11.46
unnamed: Q1.5, R50.2
unnamed: Q1.2, R51.2
unnamed: R54.1, U15.8
unnamed: JP8.3, R56.2
unnamed: JP8.1, R57.2
unnamed: R74.1, U11.51
unnamed: C48.1, C49.2, Q4.D1, Q4.G2, R60.1
unnamed: C53.2, R63.2, U19.33, Y2.3
unnamed: C54.2, R63.1, U19.32, Y2.1
unnamed: R62.1, U19.35
unnamed: R64.2, U19.28
unnamed: R65.2, U19.25
unnamed: C55.1, U19.34
unnamed: C56.1, U19.14
unnamed: R69.2, U19.30
unnamed: R70.2, U19.31
unnamed: JP9.2, U19.22
unnamed: JP10.2, U19.24
unnamed: D9.A, R85.1
unnamed: R86.2, U22.40
unnamed: R87.2, U22.39
unnamed: R88.2, U22.7
unnamed: R115.1, U22.49
unnamed: R126.1, U22.50
unnamed: R119.1, U22.46
unnamed: Q5.5, R92.2
unnamed: Q5.2, R93.2
unnamed: R96.1, U25.8
unnamed: JP15.3, R98.2
unnamed: JP15.1, R99.2
unnamed: R116.1, U22.51
unnamed: C77.1, C78.2, Q6.D1, Q6.G2, R102.1
unnamed: C82.2, R105.2, U29.33, Y3.3
unnamed: C83.2, R105.1, U29.32, Y3.1
unnamed: R104.1, U29.35
unnamed: R106.2, U29.28
unnamed: R107.2, U29.25
unnamed: C84.1, U29.34
unnamed: C85.1, U29.14
unnamed: R111.2, U29.30
unnamed: R112.2, U29.31
unnamed: JP16.2, U29.22
unnamed: JP17.2, U29.24
unnamed: D13.A, R127.1
unnamed: R128.2, U32.40
unnamed: R129.2, U32.39
unnamed: R130.2, U32.7
unnamed: R157.1, U32.49
unnamed: R168.1, U32.50
unnamed: R161.1, U32.46
unnamed: Q7.5, R134.2
unnamed: Q7.2, R135.2
unnamed: R138.1, U35.8
unnamed: JP23.3, R140.2
unnamed: JP23.1, R141.2
unnamed: R158.1, U32.51
unnamed: C106.1, C107.2, Q8.D1, Q8.G2, R144.1
unnamed: C111.2, R147.2, U39.33, Y4.3
unnamed: C112.2, R147.1, U39.32, Y4.1
unnamed: R146.1, U39.35
unnamed: R148.2, U39.28
unnamed: R149.2, U39.25
unnamed: C113.1, U39.34
unnamed: C114.1, U39.14
unnamed: R153.2, U39.30
unnamed: R154.2, U39.31
unnamed: JP24.2, U39.22
unnamed: JP25.2, U39.24
unnamed: D17.A, R169.1
unnamed: R170.2, U42.40
unnamed: R171.2, U42.39
unnamed: R172.2, U42.7
unnamed: R199.1, U42.49
unnamed: R210.1, U42.50
unnamed: R203.1, U42.46
unnamed: Q9.5, R176.2
unnamed: Q9.2, R177.2
unnamed: R180.1, U45.8
unnamed: JP30.3, R182.2
unnamed: JP30.1, R183.2
unnamed: R200.1, U42.51
unnamed: C135.1, C136.2, Q10.D1, Q10.G2, R186.1
unnamed: C140.2, R189.2, U49.33, Y5.3
unnamed: C141.2, R189.1, U49.32, Y5.1
unnamed: R188.1, U49.35
unnamed: R190.2, U49.28
unnamed: R191.2, U49.25
unnamed: C142.1, U49.34
unnamed: C143.1, U49.14
unnamed: R195.2, U49.30
unnamed: R196.2, U49.31
unnamed: JP31.2, U49.22
unnamed: JP32.2, U49.24
unnamed: D21.A, R211.1
unnamed: R212.2, U52.40
unnamed: R213.2, U52.39
unnamed: R214.2, U52.7
unnamed: R241.1, U52.49
unnamed: R252.1, U52.50
unnamed: R245.1, U52.46
unnamed: Q11.5, R218.2
unnamed: Q11.2, R219.2
unnamed: R222.1, U55.8
unnamed: JP37.3, R224.2
unnamed: JP37.1, R225.2
unnamed: R242.1, U52.51
unnamed: C164.1, C165.2, Q12.D1, Q12.G2, R228.1
unnamed: C169.2, R231.2, U59.33, Y6.3
unnamed: C170.2, R231.1, U59.32, Y6.1
unnamed: R230.1, U59.35
unnamed: R232.2, U59.28
unnamed: R233.2, U59.25
unnamed: C171.1, U59.34
unnamed: C172.1, U59.14
unnamed: R237.2, U59.30
unnamed: R238.2, U59.31
unnamed: JP38.2, U59.22
unnamed: JP39.2, U59.24
unnamed: D25.A, R253.1
unnamed: R254.2, U62.40
unnamed: R255.2, U62.39
unnamed: R256.2, U62.7
unnamed: R283.1, U62.49
unnamed: R294.1, U62.50
unnamed: R287.1, U62.46
unnamed: Q13.5, R260.2
unnamed: Q13.2, R261.2
unnamed: R264.1, U65.8
unnamed: JP44.3, R266.2
unnamed: JP44.1, R267.2
unnamed: R284.1, U62.51
unnamed: C193.1, C194.2, Q14.D1, Q14.G2, R270.1
unnamed: C198.2, R273.2, U69.33, Y7.3
unnamed: C199.2, R273.1, U69.32, Y7.1
unnamed: R272.1, U69.35
unnamed: R274.2, U69.28
unnamed: R275.2, U69.25
unnamed: C200.1, U69.34
unnamed: C201.1, U69.14
unnamed: R279.2, U69.30
unnamed: R280.2, U69.31
unnamed: JP45.2, U69.22
unnamed: JP46.2, U69.24
unnamed: D29.A, R295.1
unnamed: R296.2, U72.40
unnamed: R297.2, U72.39
unnamed: R298.2, U72.7
unnamed: R325.1, U72.49
unnamed: R336.1, U72.50
unnamed: R329.1, U72.46
unnamed: Q15.5, R302.2
unnamed: Q15.2, R303.2
unnamed: R306.1, U75.8
unnamed: JP51.3, R308.2
unnamed: JP51.1, R309.2
unnamed: R326.1, U72.51
unnamed: C222.1, C223.2, Q16.D1, Q16.G2, R312.1
unnamed: C227.2, R315.2, U79.33, Y8.3
unnamed: C228.2, R315.1, U79.32, Y8.1
unnamed: R314.1, U79.35
unnamed: R316.2, U79.28
unnamed: R317.2, U79.25
unnamed: C229.1, U79.34
unnamed: C230.1, U79.14
unnamed: R321.2, U79.30
unnamed: R322.2, U79.31
unnamed: JP52.2, U79.22
unnamed: JP53.2, U79.24
POWER_BTN: C23.1, D4.C, J8.2, R31.1
POWER_BTN1: C49.1, D5.C, J19.2, R61.1
POWER_BTN2: C78.1, D10.C, J30.2, R103.1
POWER_BTN3: C107.1, D14.C, J41.2, R145.1
POWER_BTN4: C136.1, D18.C, J52.2, R187.1
POWER_BTN5: C165.1, D22.C, J63.2, R229.1
POWER_BTN6: C194.1, D26.C, J74.2, R271.1
POWER_BTN7: C223.1, D30.C, J85.2, R313.1
PPS: R41.1, U3.53
PPS1: R83.1, U11.53
PPS2: R125.1, U22.53
PPS3: R167.1, U32.53
PPS4: R209.1, U42.53
PPS5: R251.1, U52.53
PPS6: R293.1, U62.53
PPS7: R335.1, U72.53
PROG1: R6.2, U10.6
PROG2: R52.2, U15.6
PROG3: R94.2, U25.6
PROG4: R136.2, U35.6
PROG5: R178.2, U45.6
PROG6: R220.2, U55.6
PROG7: R262.2, U65.6
PROG8: R304.2, U75.6
RTK_LV: R39.1, U3.20
RTK_LV1: R81.1, U11.20
RTK_LV2: R123.1, U22.20
RTK_LV3: R165.1, U32.20
RTK_LV4: R207.1, U42.20
RTK_LV5: R249.1, U52.20
RTK_LV6: R291.1, U62.20
RTK_LV7: R333.1, U72.20
RX2_LV: R38.1, U3.26
RX2_LV1: R80.1, U11.26
RX2_LV2: R122.1, U22.26
RX2_LV3: R164.1, U32.26
RX2_LV4: R206.1, U42.26
RX2_LV5: R248.1, U52.26
RX2_LV6: R290.1, U62.26
RX2_LV7: R332.1, U72.26
RXLV: R36.1, U3.43
RXLV1: R78.1, U11.43
RXLV2: R120.1, U22.43
RXLV3: R162.1, U32.43
RXLV4: R204.1, U42.43
RXLV5: R246.1, U52.43
RXLV6: R288.1, U62.43
RXLV7: R330.1, U72.43
SCL_LV: R9.1, U3.45
SCL_LV1: R76.1, U11.45
SCL_LV2: R118.1, U22.45
SCL_LV3: R160.1, U32.45
SCL_LV4: R202.1, U42.45
SCL_LV5: R244.1, U52.45
SCL_LV6: R286.1, U62.45
SCL_LV7: R328.1, U72.45
SDA_LV: R4.1, U3.44
SDA_LV1: R75.1, U11.44
SDA_LV2: R117.1, U22.44
SDA_LV3: R159.1, U32.44
SDA_LV4: R201.1, U42.44
SDA_LV5: R243.1, U52.44
SDA_LV6: R285.1, U62.44
SDA_LV7: R327.1, U72.44
TX2_LV: R37.1, U3.27
TX2_LV1: R79.1, U11.27
TX2_LV2: R121.1, U22.27
TX2_LV3: R163.1, U32.27
TX2_LV4: R205.1, U42.27
TX2_LV5: R247.1, U52.27
TX2_LV6: R289.1, U62.27
TX2_LV7: R331.1, U72.27
TXLV: R3.1, U3.42
TXLV1: R48.1, U11.42
TXLV2: R90.1, U22.42
TXLV3: R132.1, U32.42
TXLV4: R174.1, U42.42
TXLV5: R216.1, U52.42
TXLV6: R258.1, U62.42
TXLV7: R300.1, U72.42
USB_!RESET: C28.1, R18.1, U8.26
USB_!RESET1: C57.1, R66.1, U19.26
USB_!RESET2: C86.1, R108.1, U29.26
USB_!RESET3: C115.1, R150.1, U39.26
USB_!RESET4: C144.1, R192.1, U49.26
USB_!RESET5: C173.1, R234.1, U59.26
USB_!RESET6: C202.1, R276.1, U69.26
USB_!RESET7: C231.1, R318.1, U79.26
USB_DM: J18.8, R25.1
USB_DM1: J13.8, R69.1
USB_DM2: J27.8, R111.1
USB_DM3: J38.8, R153.1
USB_DM4: J49.8, R195.1
USB_DM5: J60.8, R237.1
USB_DM6: J71.8, R279.1
USB_DM7: J82.8, R321.1
USB_DP: J18.7, R32.1
USB_DP1: J13.7, R70.1
USB_DP2: J27.7, R112.1
USB_DP3: J38.7, R154.1
USB_DP4: J49.7, R196.1
USB_DP5: J60.7, R238.1
USB_DP6: J71.7, R280.1
USB_DP7: J82.7, R322.1
VBUS_DET: C29.1, R19.2, R21.1, U8.27
VBUS_DET1: C58.1, R67.2, R68.1, U19.27
VBUS_DET2: C87.1, R109.2, R110.1, U29.27
VBUS_DET3: C116.1, R151.2, R152.1, U39.27
VBUS_DET4: C145.1, R193.2, R194.1, U49.27
VBUS_DET5: C174.1, R235.2, R236.1, U59.27
VBUS_DET6: C203.1, R277.2, R278.1, U69.27
VBUS_DET7: C232.1, R319.2, R320.1, U79.27
VOUT: C6.1, C20.1, C27.1, J10.12, J15.6, J15.7, J15.8, J15.9, Q3.D2, R22.2, U2.1, U2.3, U12.1
VOUT1: C32.1, C47.1, C52.1, J12.6, J12.7, J12.8, J12.9, J22.12, Q4.D2, R58.2, U9.1, U9.3, U18.1
VOUT2: C61.1, C76.1, C81.1, J26.6, J26.7, J26.8, J26.9, J33.12, Q6.D2, R100.2, U21.1, U21.3, U28.1
VOUT3: C90.1, C105.1, C110.1, J37.6, J37.7, J37.8, J37.9, J44.12, Q8.D2, R142.2, U31.1, U31.3, U38.1
VOUT4: C119.1, C134.1, C139.1, J48.6, J48.7, J48.8, J48.9, J55.12, Q10.D2, R184.2, U41.1, U41.3, U48.1
VOUT5: C148.1, C163.1, C168.1, J59.6, J59.7, J59.8, J59.9, J66.12, Q12.D2, R226.2, U51.1, U51.3, U58.1
VOUT6: C177.1, C192.1, C197.1, J70.6, J70.7, J70.8, J70.9, J77.12, Q14.D2, R268.2, U61.1, U61.3, U68.1
VOUT7: C206.1, C221.1, C226.1, J81.6, J81.7, J81.8, J81.9, J88.12, Q16.D2, R310.2, U71.1, U71.3, U78.1
V_BATT: C3.1, C15.1, C17.1, D7.A, MEAS2.2, MEAS2.4, U4.1, U4.3, U7.2, U7.3, U10.9, U10.10
V_BATT1: C41.1, C42.1, C44.1, D6.A, MEAS1.2, MEAS1.4, U14.2, U14.3, U15.9, U15.10, U17.1, U17.3
V_BATT2: C70.1, C71.1, C73.1, D11.A, MEAS3.2, MEAS3.4, U24.2, U24.3, U25.9, U25.10, U27.1, U27.3
V_BATT3: C99.1, C100.1, C102.1, D15.A, MEAS4.2, MEAS4.4, U34.2, U34.3, U35.9, U35.10, U37.1, U37.3
V_BATT4: C128.1, C129.1, C131.1, D19.A, MEAS5.2, MEAS5.4, U44.2, U44.3, U45.9, U45.10, U47.1, U47.3
V_BATT5: C157.1, C158.1, C160.1, D23.A, MEAS6.2, MEAS6.4, U54.2, U54.3, U55.9, U55.10, U57.1, U57.3
V_BATT6: C186.1, C187.1, C189.1, D27.A, MEAS7.2, MEAS7.4, U64.2, U64.3, U65.9, U65.10, U67.1, U67.3
V_BATT7: C215.1, C216.1, C218.1, D31.A, MEAS8.2, MEAS8.4, U74.2, U74.3, U75.9, U75.10, U77.1, U77.3
V_RAW: C16.1, C22.2, D2.C, D7.C, Q3.S2, R26.2, R31.2, U10.1, U10.2
V_RAW1: C45.1, C48.2, D6.C, D8.C, Q4.S2, R60.2, R61.2, U15.1, U15.2
V_RAW2: C74.1, C77.2, D11.C, D12.C, Q6.S2, R102.2, R103.2, U25.1, U25.2
V_RAW3: C103.1, C106.2, D15.C, D16.C, Q8.S2, R144.2, R145.2, U35.1, U35.2
V_RAW4: C132.1, C135.2, D19.C, D20.C, Q10.S2, R186.2, R187.2, U45.1, U45.2
V_RAW5: C161.1, C164.2, D23.C, D24.C, Q12.S2, R228.2, R229.2, U55.1, U55.2
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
